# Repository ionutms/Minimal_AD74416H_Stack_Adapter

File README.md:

# Minimal_AD74416H_Stack_Adapter

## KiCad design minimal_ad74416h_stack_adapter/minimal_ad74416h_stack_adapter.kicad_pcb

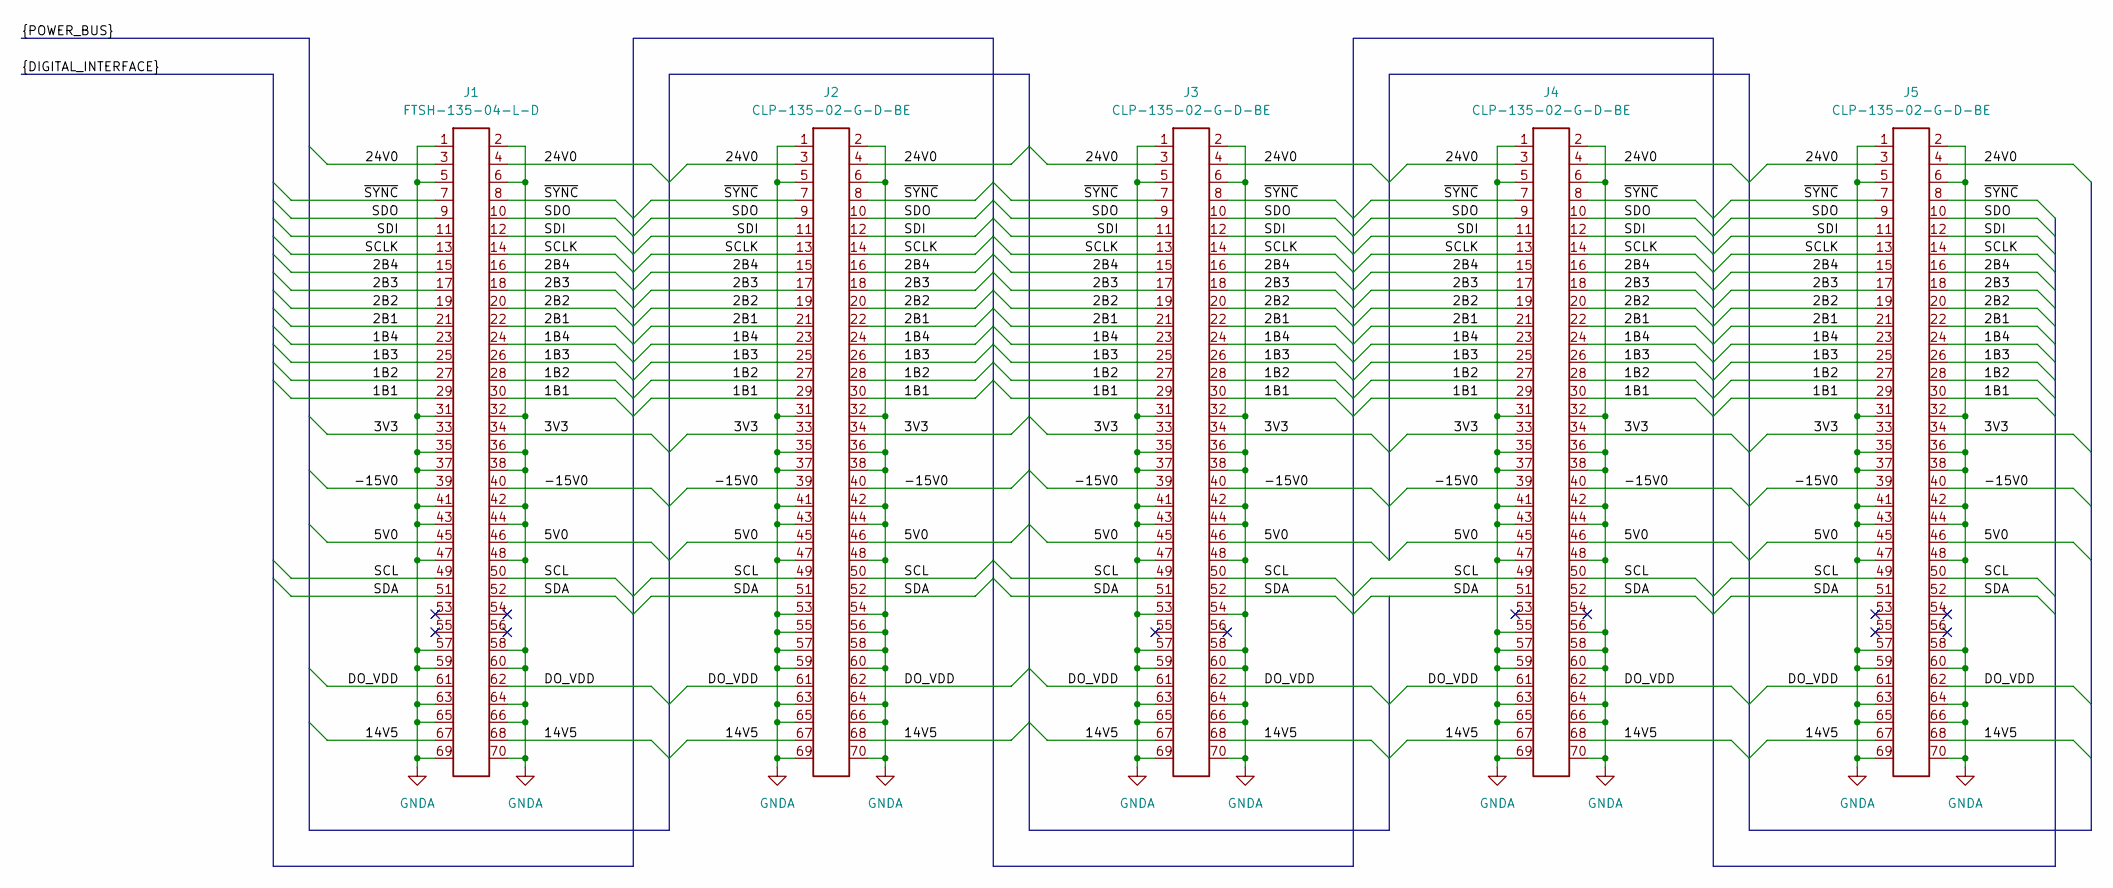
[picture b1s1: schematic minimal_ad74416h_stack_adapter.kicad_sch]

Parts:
J1: FTSH-135-04-L-D; Current Rating (A) 5.2; Voltage Rating (V) 300; MPN FTSH-135-04-L-D
J2, J3, J4, J5: CLP-135-02-G-D-BE; Current Rating (A) 5.2; Voltage Rating (V) 300; MPN CLP-135-02-G-D-BE

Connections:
/1B1: J1.29, J1.30, J2.29, J2.30, J3.29, J3.30, J4.29, J4.30, J5.29, J5.30
/1B2: J1.27, J1.28, J2.27, J2.28, J3.27, J3.28, J4.27, J4.28, J5.27, J5.28
/1B3: J1.25, J1.26, J2.25, J2.26, J3.25, J3.26, J4.25, J4.26, J5.25, J5.26
/1B4: J1.23, J1.24, J2.23, J2.24, J3.23, J3.24, J4.23, J4.24, J5.23, J5.24
/2B1: J1.21, J1.22, J2.21, J2.22, J3.21, J3.22, J4.21, J4.22, J5.21, J5.22
/2B2: J1.19, J1.20, J2.19, J2.20, J3.19, J3.20, J4.19, J4.20, J5.19, J5.20
/2B3: J1.17, J1.18, J2.17, J2.18, J3.17, J3.18, J4.17, J4.18, J5.17, J5.18
/2B4: J1.15, J1.16, J2.15, J2.16, J3.15, J3.16, J4.15, J4.16, J5.15, J5.16
/3V3: J1.33, J1.34, J2.33, J2.34, J3.33, J3.34, J4.33, J4.34, J5.33, J5.34
/5V0: J1.45, J1.46, J2.45, J2.46, J3.45, J3.46, J4.45, J4.46, J5.45, J5.46
/14V5: J1.67, J1.68, J2.67, J2.68, J3.67, J3.68, J4.67, J4.68, J5.67, J5.68
/24V0: J1.3, J1.4, J2.3, J2.4, J3.3, J3.4, J4.3, J4.4, J5.3, J5.4
/-15V0: J1.39, J1.40, J2.39, J2.40, J3.39, J3.40, J4.39, J4.40, J5.39, J5.40
/DO_VDD: J1.61, J1.62, J2.61, J2.62, J3.61, J3.62, J4.61, J4.62, J5.61, J5.62
/SCL: J1.49, J1.50, J2.49, J2.50, J3.49, J3.50, J4.49, J4.50, J5.49, J5.50
/SCLK: J1.13, J1.14, J2.13, J2.14, J3.13, J3.14, J4.13, J4.14, J5.13, J5.14
/SDA: J1.51, J1.52, J2.51, J2.52, J3.51, J3.52, J4.51, J4.52, J5.51, J5.52
/SDI: J1.11, J1.12, J2.11, J2.12, J3.11, J3.12, J4.11, J4.12, J5.11, J5.12
/SDO: J1.9, J1.10, J2.9, J2.10, J3.9, J3.10, J4.9, J4.10, J5.9, J5.10
/~SYNC: J1.7, J1.8, J2.7, J2.8, J3.7, J3.8, J4.7, J4.8, J5.7, J5.8
GNDA: J1.1, J1.2, J1.5, J1.6, J1.31, J1.32, J1.35, J1.36, J1.37, J1.38, J1.41, J1.42, J1.43, J1.44, J1.47, J1.48, J1.57, J1.58, J1.59, J1.60, J1.63, J1.64, J1.65, J1.66, J1.69, J1.70, J2.1, J2.2, J2.5, J2.6, J2.31, J2.32, J2.35, J2.36, J2.37, J2.38, J2.41, J2.42, J2.43, J2.44, J2.47, J2.48, J2.53, J2.54, J2.55, J2.56, J2.57, J2.58, J2.59, J2.60, J2.63, J2.64, J2.65, J2.66, J2.69, J2.70, J3.1, J3.2, J3.5, J3.6, J3.31, J3.32, J3.35, J3.36, J3.37, J3.38, J3.41, J3.42, J3.43, J3.44, J3.47, J3.48, J3.53, J3.54, J3.57, J3.58, J3.59, J3.60, J3.63, J3.64, J3.65, J3.66, J3.69, J3.70, J4.1, J4.2, J4.5, J4.6, J4.31, J4.32, J4.35, J4.36, J4.37, J4.38, J4.41, J4.42, J4.43, J4.44, J4.47, J4.48, J4.55, J4.56, J4.57, J4.58, J4.59, J4.60, J4.63, J4.64, J4.65, J4.66, J4.69, J4.70, J5.1, J5.2, J5.5, J5.6, J5.31, J5.32, J5.35, J5.36, J5.37, J5.38, J5.41, J5.42, J5.43, J5.44, J5.47, J5.48, J5.57, J5.58, J5.59, J5.60, J5.63, J5.64, J5.65, J5.66, J5.69, J5.70

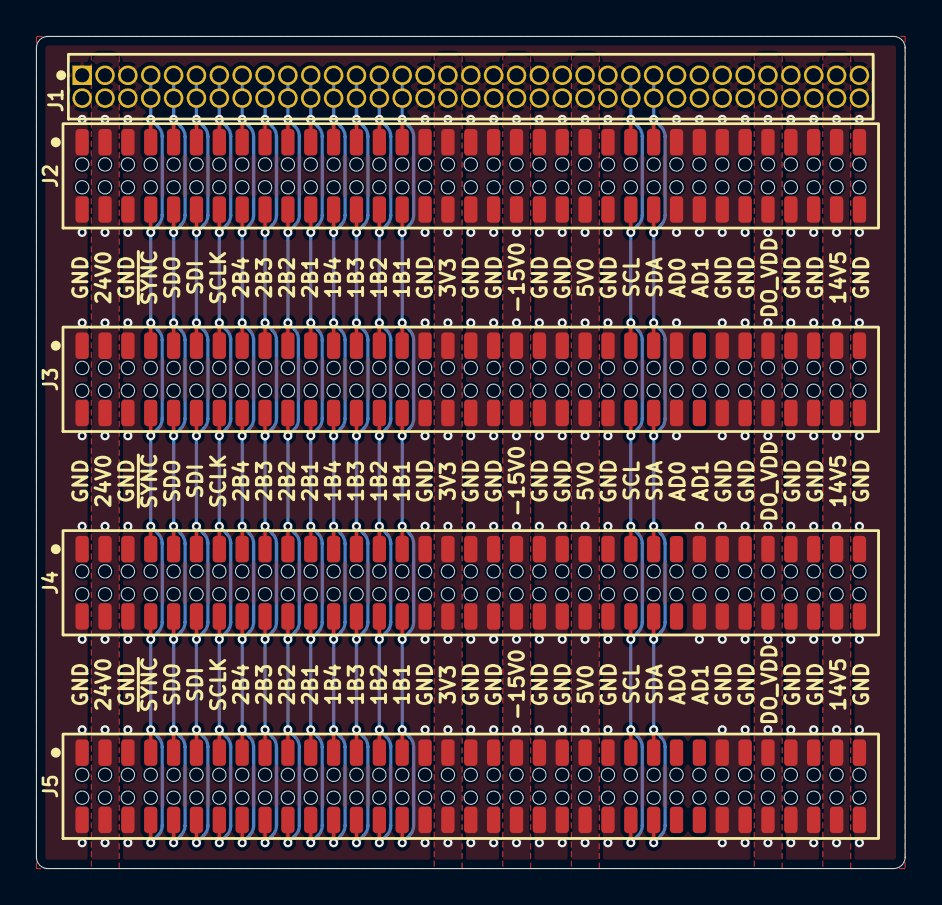
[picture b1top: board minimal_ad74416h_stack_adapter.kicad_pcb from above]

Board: 4 copper layers, 48.3 x 46.2 mm, 5 parts (0 on the bottom side), 21 nets.

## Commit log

2025-10-11 Add KiCAD project files and KiCAD_Symbols_Generator submodule
2025-10-11 chore: update workflows and kicad config from central repository
2025-10-11 backup
2025-10-11 Update KiCad documentation for minimal_ad74416h_stack_adapter (schematics and PCB renders)
2025-10-11 Update KiCAD configuration
2025-10-12 cleanup
2025-10-18 Update KiCAD configuration settings
